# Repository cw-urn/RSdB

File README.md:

# RSdB
> What is this?
- RSdB (rim shot dB) is a general usage dB meter with an OLED display, powered by the MEMS MSM261DGT003 and a Seeed XIAO RP2040.
> How do you use it?
- Plug straight into a generic USB-C power bank, and start measuring right away!
> Why did I make this?
- Primarily to not annoy my neighbours. It's nice knowing how loud I'm playing at any given moment so I know I need to chill down on the heavy hits. Secondarily, I didn't have any major experience with PDM microphones before, so I thought this would be a great place to start.

# Firmware
Firmware can be found at main/firmware.

The microphone I chose doesn't send traditional audio signals, instead it sends a single stream of ones and zeros at roughly 2 MHz. So one bit per clock pulse. The important part here is that stream having a bunch of repeating numbers after another.

If it sends a bunch of ones, then the sound pressure is high, and sends a bunch of zeros when it's low. The XIAO generates the clock, and reads the DATA pin at the same time. Once enough bits have accumulated, a decimation filter takes over, and it applies a low-pass sinc filter across every 128 bits and collapses them into a single 16-bit PCM sample, throwing away the ultrasonic noise the oversampling introduced and leaving just the audio band. This produces 16,000 audio samples per second.

From there, the firmware squares and accumulates every sample over a one-second window, computes the RMS amplitude (a measure of average signal energy that correctly handles the fact that audio oscillates both positive and negative), converts the result to dBFS using a base-10 logarithm, and then applies a sensitivity offset derived from the microphone's datasheet to produce an approximate reading in dB SPL. This calculation part was really tricky and I just couldn't figure out the math myself. Used AI for that part.

# PCB

<hr>

<hr>

## BOM

| Item | Quantity | Price | Funding required | Link |
| :---: | :---: | :---: | :---: | :---: |
| PCB | 1 | 16.26\* | Yes | [JLCPCB](https://jlcpcb.com/) |
| SSD1306 128×64 Mono 0.96 Inch I2C OLED Display | 1 | - | No | None |
| Seeed Studio XIAO RP2040 | 1 | - | No | None |

\* Note that price might fluctuate based on LCSC component prices, and the availability of coupons at the time of purchase. Includes PCBA.

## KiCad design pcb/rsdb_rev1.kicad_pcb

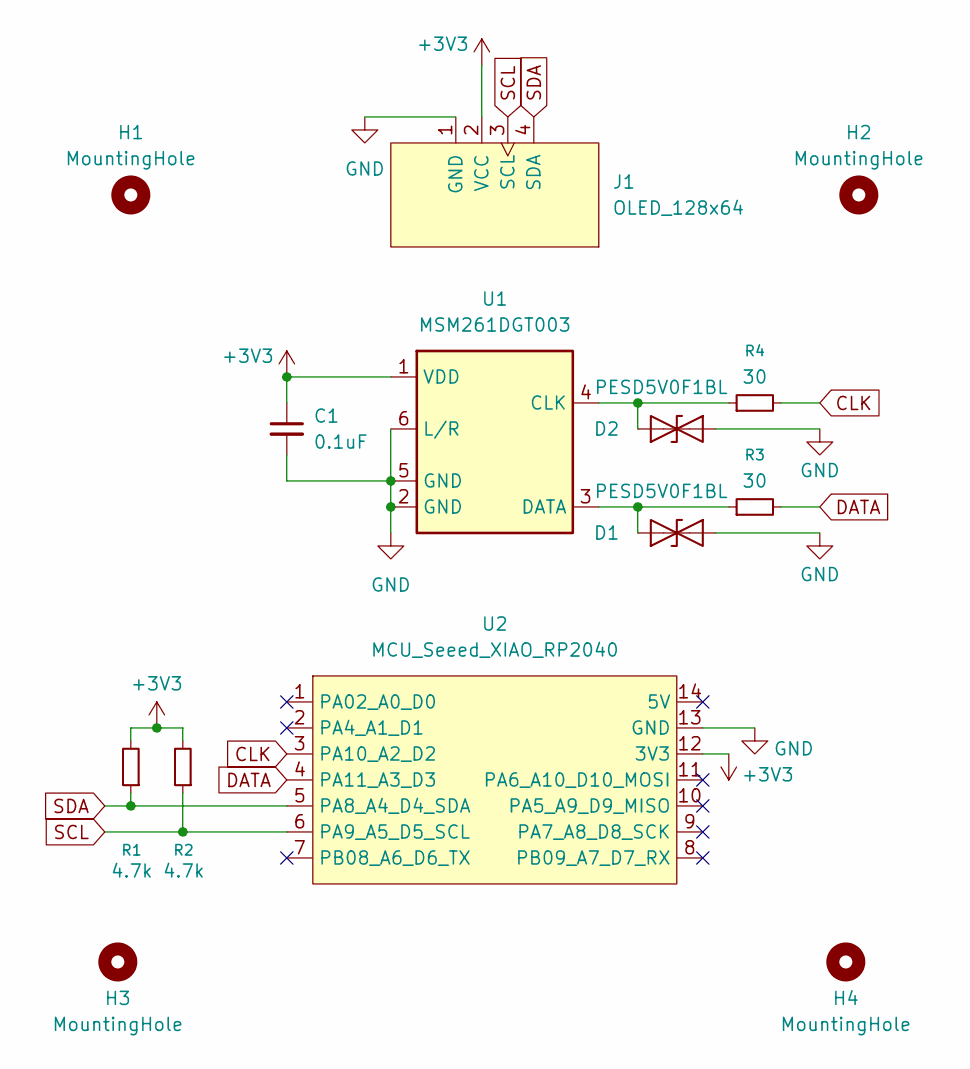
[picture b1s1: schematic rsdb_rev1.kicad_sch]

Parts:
C1: 0.1uF; C_0603_1608Metric_Pad1.08x0.95mm_HandSolder
D1, D2: PESD5V0F1BL; D_0402_1005Metric_Pad0.77x0.64mm_HandSolder
H1, H2, H3, H4: MountingHole; MountingHole_2.2mm_M2
J1: OLED_128x64
R1, R2: 4.7k; R_0603_1608Metric_Pad0.98x0.95mm_HandSolder
R3, R4: 30; R_0603_1608Metric_Pad0.98x0.95mm_HandSolder
U1: MSM261DGT003
U2: MCU_Seeed_XIAO_RP2040; Seeed_XIAO_RP2040

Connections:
+3V3: C1.1, J1.2 (VCC), R1.2, R2.2, U1.1 (VDD), U2.12 (3V3)
CLK: R4.2, U2.3 (PA10_A2_D2)
DATA: R3.2, U2.4 (PA11_A3_D3)
GND: C1.2, D1.2 (A2), D2.2 (A2), J1.1 (GND), U1.2 (GND), U1.5 (GND), U1.6 (L/R), U2.13 (GND)
unnamed: D1.1 (A1), R3.1, U1.3 (DATA)
unnamed: D2.1 (A1), R4.1, U1.4 (CLK)
SCL: J1.3 (SCL), R2.1, U2.6 (PA9_A5_D5_SCL)
SDA: J1.4 (SDA), R1.1, U2.5 (PA8_A4_D4_SDA)

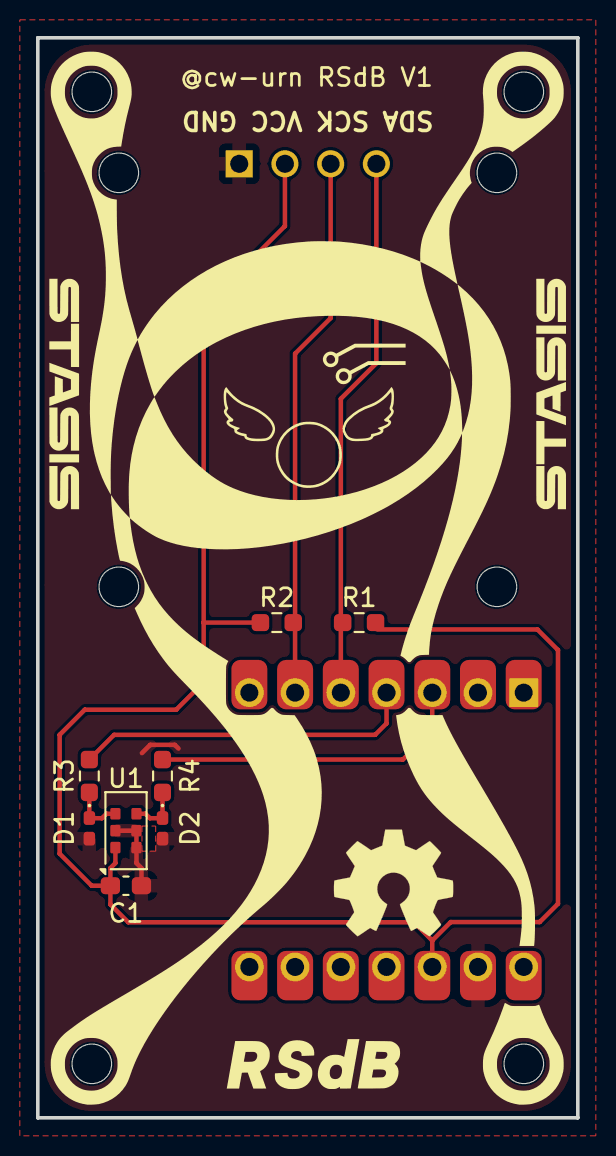
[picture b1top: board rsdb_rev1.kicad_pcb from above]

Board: 2 copper layers, 30.0 x 60.0 mm, 14 parts (0 on the bottom side), 8 nets.

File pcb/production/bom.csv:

Designator,Footprint,Quantity,Value,LCSC Part #
C1,0603,1,0.1uF,
"D1, D2",0402,2,PESD5V0F1BL,
J1,OLED_128x64,1,OLED_128x64,
"R1, R2",0603,2,4.7k,
"R3, R4",0603,2,30,
U1,MSM261DGT003,1,MSM261DGT003,
U2,Seeed_XIAO_RP2040,1,MCU_Seeed_XIAO_RP2040,

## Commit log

2026-06-16 deleted x.txt
2026-06-17 final?
2026-06-18 firmware
2026-06-18 readme
2026-06-22 readme 2
2026-06-22 added bom
2026-06-26 firmware and readme
